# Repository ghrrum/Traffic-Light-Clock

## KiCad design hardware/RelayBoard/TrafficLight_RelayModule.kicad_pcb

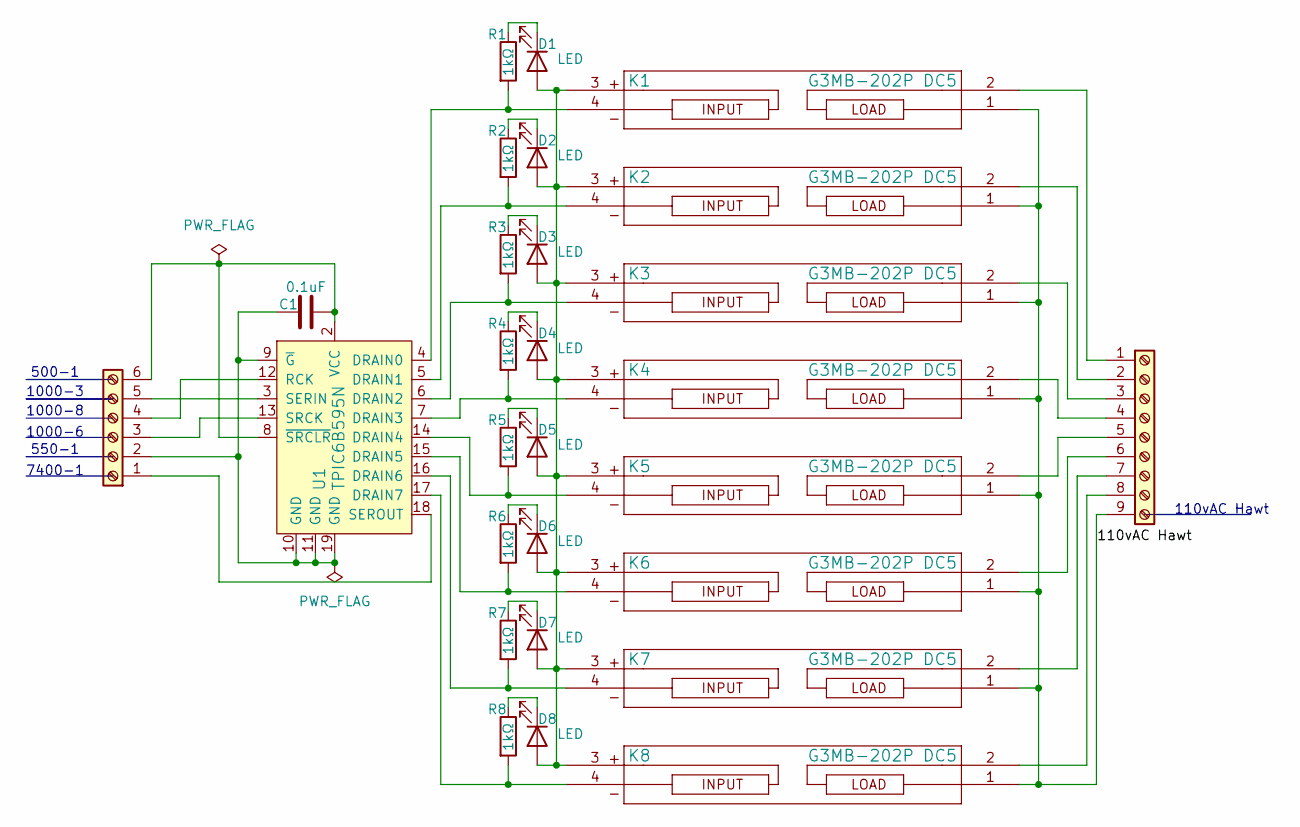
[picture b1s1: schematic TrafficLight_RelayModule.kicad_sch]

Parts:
C1: 0.1uF; C_0805_2012Metric
D1, D2, D3, D4, D5, D6, D7, D8: LED; LED_0805_2012Metric
J1: Screw_Terminal_01x09; TerminalBlock_MaiXu_MX126-5.0-09P_1x09_P5.00mm
J2: Screw_Terminal_01x06; TerminalBlock_MaiXu_MX126-5.0-06P_1x06_P5.00mm
K1, K2, K3, K4, K5, K6, K7, K8: G3MB-202P DC5; G3MB_202P_DC5
R1, R2, R3, R4, R5, R6, R7, R8: 1kΩ; R_0805_2012Metric
U1: TPIC6B595N; MPN TPIC6B595N; Digi-Key_PN 296-1956-5-ND

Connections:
unnamed: D1.2 (A), D2.2 (A), D3.2 (A), D4.2 (A), D5.2 (A), D6.2 (A), D7.2 (A), D8.2 (A), K1.3, K2.3, K3.3, K4.3, K5.3, K6.3, K7.3, K8.3
unnamed: D1.1 (K), R1.1
unnamed: D2.1 (K), R2.1
unnamed: D3.1 (K), R3.1
unnamed: D4.1 (K), R4.1
unnamed: D5.1 (K), R5.1
unnamed: D6.1 (K), R6.1
unnamed: D7.1 (K), R7.1
unnamed: D8.1 (K), R8.1
unnamed: J1.1, K1.2
unnamed: J1.2, K2.2
unnamed: J1.3, K3.2
unnamed: J1.4, K4.2
unnamed: J1.5, K5.2
unnamed: J1.6, K6.2
unnamed: J1.7, K7.2
unnamed: J1.8, K8.2
unnamed: J1.9, K1.1, K2.1, K3.1, K4.1, K5.1, K6.1, K7.1, K8.1
unnamed: J2.1, U1.18 (SEROUT)
unnamed: C1.1, J2.2, U1.9 (~G), U1.10 (GND), U1.11 (GND), U1.19 (GND)
unnamed: J2.3, U1.13 (SRCK)
unnamed: J2.4, U1.12 (RCK)
unnamed: J2.5, U1.3 (SERIN)
unnamed: C1.2, J2.6, U1.2 (VCC), U1.8 (~SRCLR)
unnamed: K1.4, R1.2, U1.4 (DRAIN0)
unnamed: K2.4, R2.2, U1.5 (DRAIN1)
unnamed: K3.4, R3.2, U1.6 (DRAIN2)
unnamed: K4.4, R4.2, U1.7 (DRAIN3)
unnamed: K5.4, R5.2, U1.14 (DRAIN4)
unnamed: K6.4, R6.2, U1.15 (DRAIN5)
unnamed: K7.4, R7.2, U1.16 (DRAIN6)
unnamed: K8.4, R8.2, U1.17 (DRAIN7)

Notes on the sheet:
1000-8
1000-3
550-1
1000-6
110vAC Hawt
7400-1
500-1

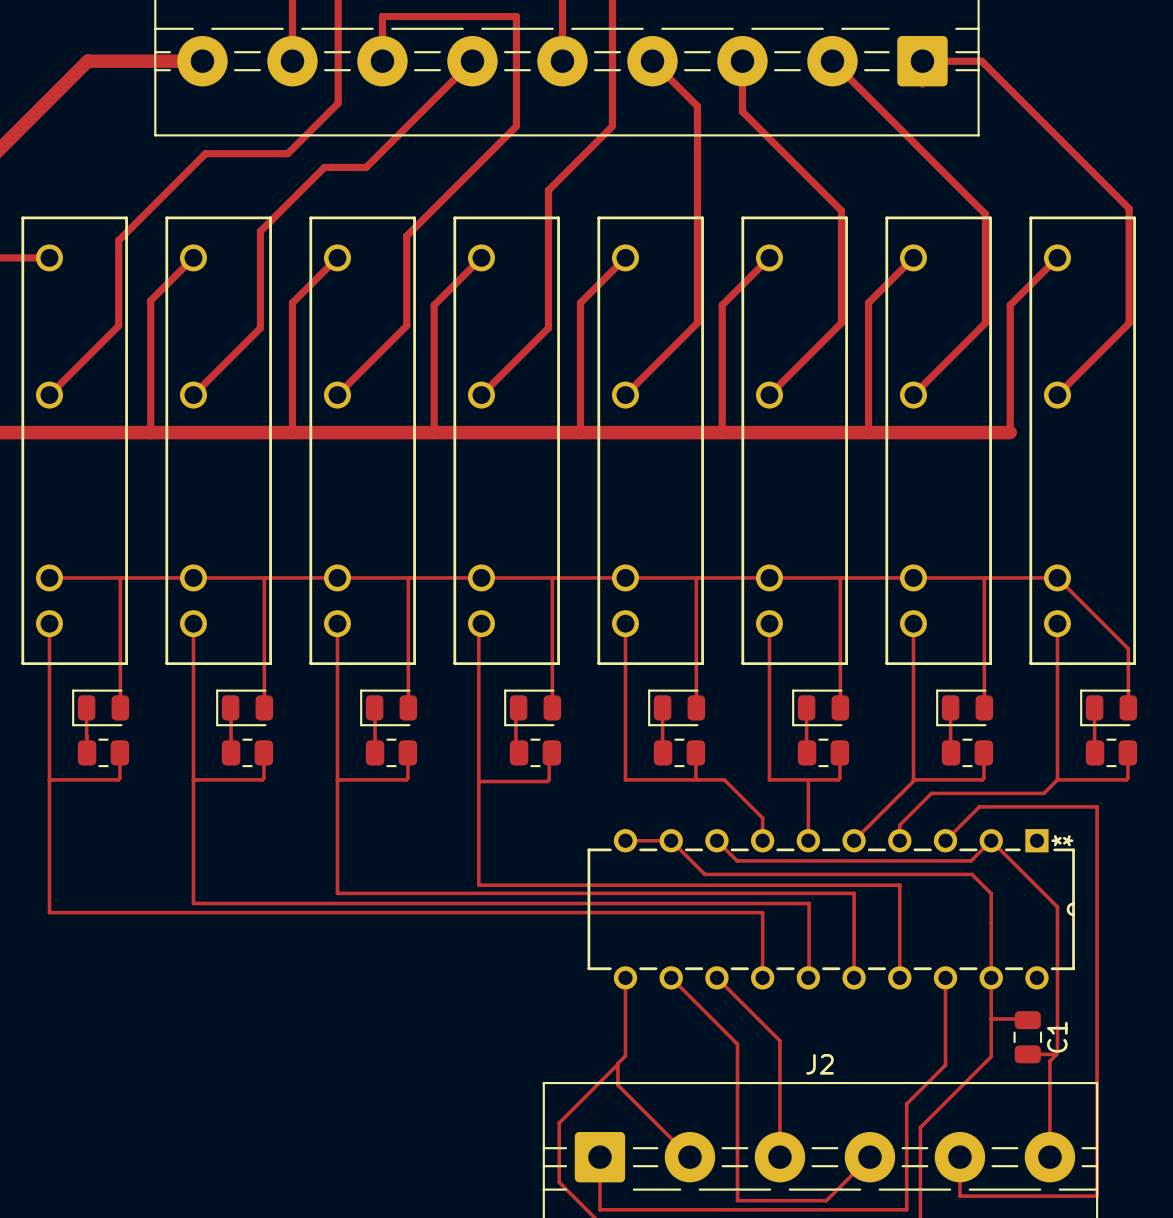
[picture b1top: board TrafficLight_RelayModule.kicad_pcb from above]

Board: 2 copper layers, 28 parts (0 on the bottom side), 32 nets.
